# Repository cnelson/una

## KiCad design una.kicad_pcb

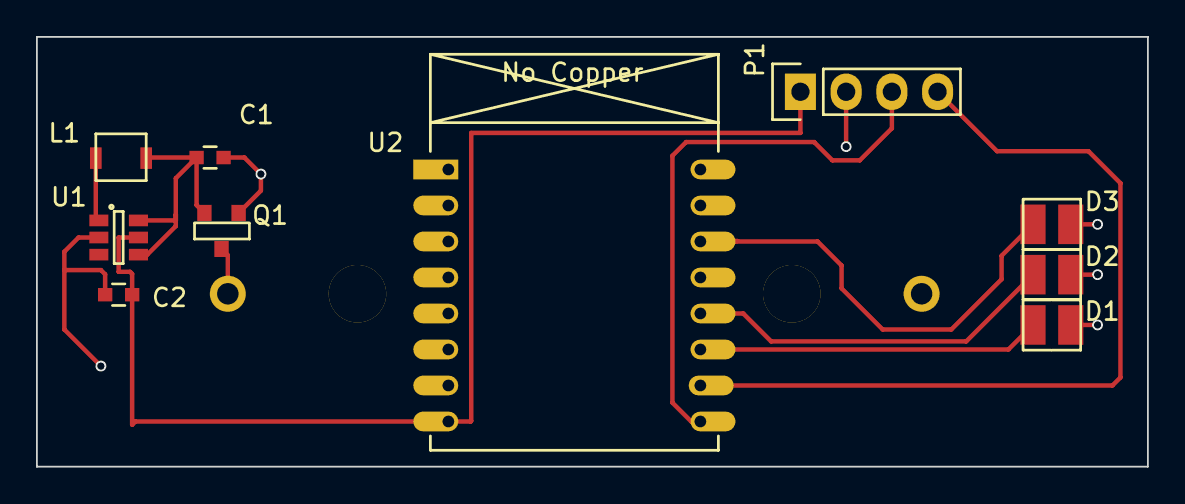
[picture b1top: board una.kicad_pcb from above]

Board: 2 copper layers, 61.7 x 23.9 mm, 11 parts (1 on the bottom side), 10 nets.

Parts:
BT1: BATT; MPD_6S_2_3A
C1, C2: 4.7uF; C_0603
D1: LED_RED; EBAY_LED
D2: LED_GREEN; EBAY_LED
D3: LED_BLUE; EBAY_LED
L1: 4.7uH; VLF3012AT-4R7MR74
P1: PROGRAMMING_PORT; Pin_Header_Straight_1x04
Q1: Q_PMOS_DSG; DMP2305U-7
U1: AAT1217-3.3; SOT-23-6
U2: ESP-07; ESP-07v2

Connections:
unnamed: BT1.1, Q1.1
unnamed: BT1.2, C1.1, C2.1, D1.1, D2.1, D3.1, P1.2, Q1.3, U1.2, U2.16
unnamed: C1.2, L1.2, Q1.2, U1.4, U1.6
unnamed: C2.2, P1.1, U1.5, U2.8
unnamed: D1.2, U2.11
unnamed: D2.2, U2.12
unnamed: D3.2, U2.14
unnamed: L1.1, U1.1
unnamed: P1.3, U2.9
unnamed: P1.4, U2.10
